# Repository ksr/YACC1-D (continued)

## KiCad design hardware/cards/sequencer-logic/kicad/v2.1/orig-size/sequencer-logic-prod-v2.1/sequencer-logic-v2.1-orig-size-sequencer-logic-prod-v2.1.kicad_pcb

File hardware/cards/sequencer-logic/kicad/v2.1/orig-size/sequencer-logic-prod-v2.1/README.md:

# sequencer-logic-v2.1-orig-size-sequencer-logic-prod-v2.1 — KiCad conversion

Generated 2026-09-23 by `tools/eagle_to_kicad_all.py` from the Eagle design `Sequencer-Logic-Prod-V2.1` in `hardware/cards/sequencer-logic/eagle/v2.1/orig size/`. **The Eagle files are the record of what was designed and built; this KiCad project is derived from them and is regenerated from scratch on every run of the tool** (hand edits here will be lost - once a card is edited in KiCad, remove it from the tool's list). This revision was never fabricated (or its build status is unknown, see `hardware/FABRICATED.md`).

## Files

| File | What it is |
|---|---|
| `sequencer-logic-v2.1-orig-size-sequencer-logic-prod-v2.1.kicad_pro` | project; OSH Park rules (6 mil track, 5 mil clearance, 10 mil drill, 4 mil annular) |
| `sequencer-logic-v2.1-orig-size-sequencer-logic-prod-v2.1.kicad_sch` | root sheet; 10 sub-sheet(s) `sequencer-logic-v2.1-orig-size-sequencer-logic-prod-v2.1-sheetN.kicad_sch` mirror the Eagle sheets |
| `sequencer-logic-v2.1-orig-size-sequencer-logic-prod-v2.1-eagle.kicad_sym` | project symbol library generated from the Eagle libraries used (units = Eagle gates) |
| `sequencer-logic-v2.1-orig-size-sequencer-logic-prod-v2.1.kicad_pcb` | the board: 4 copper layers, 106 footprints, 4408 track segments, 539 vias |
| `sequencer-logic-v2.1-orig-size-sequencer-logic-prod-v2.1-eagle.pretty/` | project footprint library extracted from the imported board |
| `reports/` | ERC (`erc.json`), DRC (`drc.json`), schematic PDF, board renders (`-top.png`, `-bottom.png`), netlist + `netlist-compare.txt` |

## Proof

Schematic-vs-board netlist comparison (`tools/kicad/compare_netlists.py`: every (reference, pad) partition must be identical): **MATCH (282/282 nets)**

```
  same connectivity, different net name: [('/Sheet 1/-DO-INT', '-DO-INT'), ('/Sheet 1/CNT-CLK', 'CNT-CLK'), ('/Sheet 1/COUNT-FAULT', 'COUNT-FAULT'), ('/Sheet 1/DO-HALT', 'DO-HALT'), ('/Sheet 1/HALT-CLR', 'HALT-CLR'), ('/Sheet 1/LD-INS-REG1', 'LD-INS-REG1'), ('/Sheet 1/UCODE-CLK', 'UCODE-CLK'), ('/Sheet 2/SPARE3', 'SPARE3'), ('/Sheet 3/INT-EDGE', 'INT-EDGE'), ('/Sheet 5/-FP-HALT', '-FP-HALT'), ('/Sheet 5/-HALT-CONT', '-HALT-CONT'), ('/Sheet 5/EXTERNAL-SINGLESTEP-CLK', 'EXTERNAL-SINGLESTEP-CLK'), ('/Sheet 5/FP-CLKL', 'FP-CLKL'), ('/Sheet 5/FP-SINGLE-STEP-CLK', 'FP-SINGLE-STEP-CLK'), ('/Sheet 5/FP-SS', 'FP-SS'), ('/Sheet 6/-ONE-OPERAND-SEL', '-ONE-OPERAND-SEL'), ('Net-(-INT-PULLUP0-Pad1)', 'N$49'), ('Net-(.0-PadA)', 'N$59'), ('Net-(IC1A-A1)', 'N$2'), ('Net-(IC1A-A2)', 'N$3'), ('Net-(IC1A-A3)', 'N$10'), ('Net-(IC1A-A4)', 'N$23'), ('Net-(IC1B-A1)', 'N$34'), ('Net-(IC1B-A2)', 'N$35'), ('Net-(IC1B-A3)', 'N$36'), ('Net-(IC1B-A4)', 'N$37'), ('Net-(IC2A-A1)', 'N$7'), ('Net-(IC2A-A2)', 'N$8'), ('Net-(IC2A-A3)', 'N$9'), ('Net-(IC2A-A4)', 'N$11'), ('Net-(IC2B-A1)', 'N$12'), ('Net-(IC2B-A2)', 'N$13'), ('Net-(IC2B-A3)', 'N$14'), ('Net-(IC2B-A4)', 'N$15'), ('Net-(IC3-D1)', 'N$19'), ('Net-(IC3-D2)', 'N$20'), ('Net-(IC3-D3)', 'N$21'), ('Net-(IC3-D4)', 'N$22'), ('Net-(IC4-D1)', 'N$5'), ('Net-(IC4-D2)', 'N$6'), ('Net-(IC4-D3)', 'N$17'), ('Net-(IC4-D4)', 'N$18'), ('Net-(IC5-UP)', 'N$1'), ('Net-(IC7A-O)', 'N$31'), ('Net-(IC7C-I0)', 'N$40'), ('Net-(IC10A-I1)', 'N$55'), ('Net-(IC10A-O)', 'COUNT-RESET'), ('Net-(IC10B-I0)', 'N$39'), ('Net-(IC10B-I1)', 'N$38'), ('Net-(IC10C-I0)', 'N$72'), ('Net-(IC10C-I1)', 'N$71'), ('Net-(IC10C-O)', 'N$60'), ('Net-(IC10D-O)', 'N$26'), ('Net-(IC11B-I)', 'N$27'), ('Net-(IC11B-O)', 'N$29'), ('Net-(IC11E-I)', 'N$42'), ('Net-(IC11E-O)', 'N$46'), ('Net-(IC11F-I)', 'N$43'), ('Net-(IC11F-O)', 'N$41'), ('Net-(IC12B-I0)', 'N$53'), ('Net-(IC12B-O)', 'N$58'), ('Net-(IC12C-I0)', 'N$28'), ('Net-(IC12C-I1)', 'N$24'), ('Net-(IC12D-O)', 'N$54'), ('Net-(IC21A-I1)', 'N$25'), ('Net-(IC21C-O)', 'N$48'), ('Net-(IC22B-CLK)', 'N$33'), ('Net-(IC23A-I0)', 'FP-RESET'), ('Net-(IC23B-I1)', 'FP-EXECUTE'), ('Net-(IC23C-O)', 'N$32'), ('Net-(IC24A-I0)', 'N$70'), ('Net-(IC24A-O)', 'N$67'), ('Net-(IC24B-I0)', 'N$56'), ('Net-(IC24B-I1)', 'N$52'), ('Net-(IC24D-O)', 'N$47'), ('Net-(IC29B-I1)', 'N$4'), ('Net-(IC29C-I0)', 'N$51'), ('Net-(IC29D-O)', 'N$57'), ('Net-(IC30A-O)', 'N$44'), ('Net-(IC31A-I0)', 'FP-FREERUN'), ('Net-(IC31C-I1)', 'HARD-RESET1'), ('Net-(IC31D-I1)', 'FP-CLKH'), ('Net-(IC33A-A1)', 'N$62'), ('Net-(IC33A-A2)', 'N$63'), ('Net-(IC33A-A3)', 'N$64'), ('Net-(IC33A-A4)', 'N$65'), ('Net-(IC33B-A1)', 'N$66'), ('Net-(IC33B-A2)', 'N$68'), ('Net-(IC33B-A3)', 'N$69'), ('Net-(IC33B-A4)', 'N$61'), ('Net-(IC35A-O)', 'N$45'), ('Net-(IC36C-O)', 'N$16'), ('Net-(PWR0-PadA)', 'N$30'), ('SINGLE-STEP{slash}WAIT', 'SINGLE-STEP/WAIT')]
```

## Readability

`tools/kicad/sch_overlaps.py` over every sheet: text over text 14, text over a symbol body 22, text crossed by a line 50, items off the drawing frame or on the title block 0. What is left is mostly the Eagle drawing itself (parts placed that close in Eagle) or KiCad drawing pin numbers centred on short pins.

## Residual ERC / DRC

ERC by type: endpoint_off_grid 89, isolated_pin_label 18, unconnected_wire_endpoint 14.
`isolated_pin_label` = the converter's per-net global labels (cosmetic); `power_pin_not_driven` / unused-unit notes are the same ones KiCad's own Eagle importer leaves. `unconnected_wire_endpoint` / `pin_not_connected` = wire stubs Eagle leaves bare (mostly net wires ending on a bus, which is drawn as graphics here); since 2026-09-23 the converter no longer hangs a label on every such end (that was most of the label clutter), so they show as KiCad warnings.

DRC by type: clearance 9, items_not_allowed 2, lib_footprint_mismatch 3, shorting_items 61, silk_edge_clearance 25, silk_over_copper 199, silk_overlap 199, starved_thermal 1, text_height 38, text_thickness 36, track_width 199; unconnected items 4; schematic parity 0.
Silk-over-pad and clearance notes reflect the Eagle design as drawn; unconnected items are Eagle airwires (parts the design left unrouted).

Converter: converted: 276 symbols, 1063 wires, 508 labels, 226 junctions, 1 bus lines, 25 no-connects

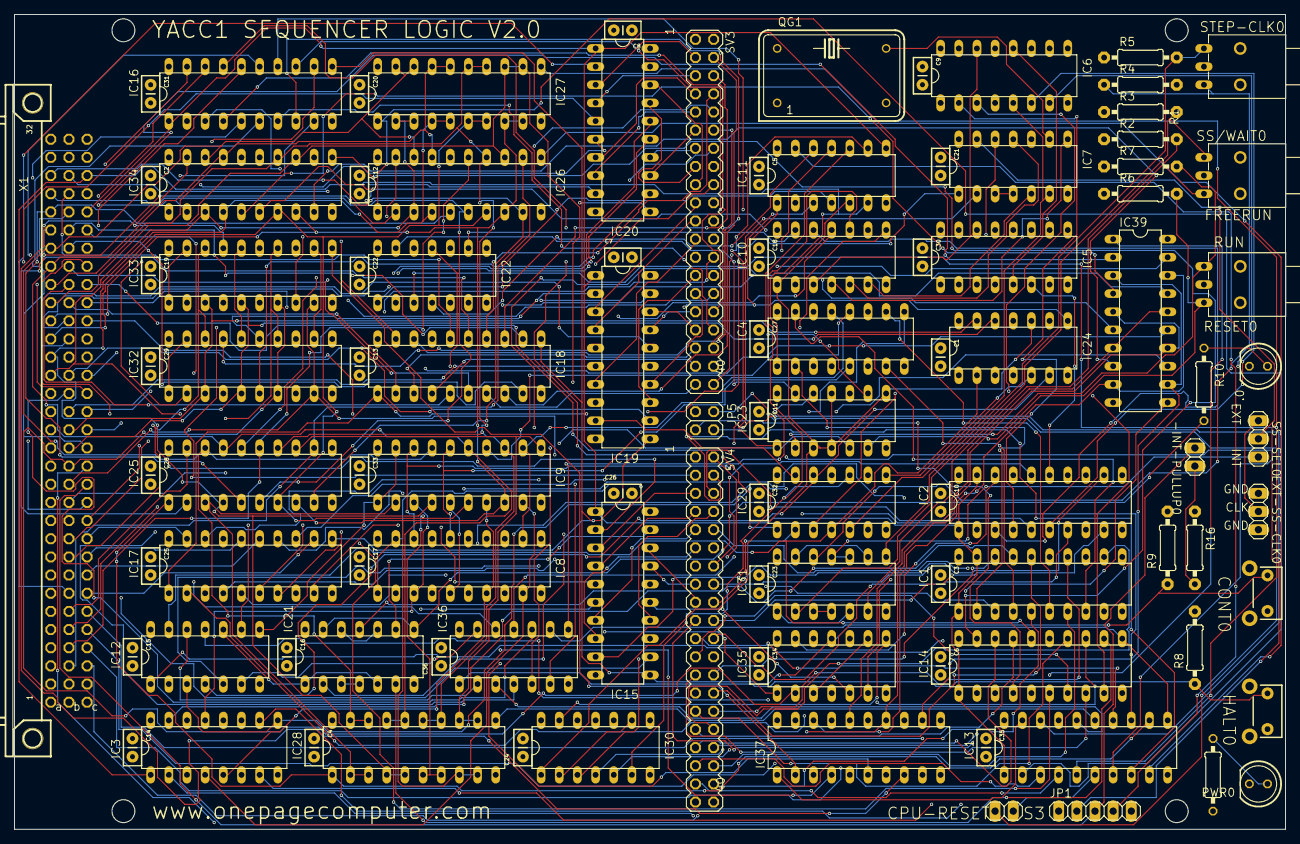
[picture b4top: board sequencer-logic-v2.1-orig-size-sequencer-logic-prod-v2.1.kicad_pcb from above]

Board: 4 copper layers, 177.8 x 114.0 mm, 106 parts (0 on the bottom side), 282 nets.

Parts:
-INT-PULLUP0: 1X02
.0: OUT; LED5MM
C1, C2, C3, C4, C5, C6, C7, C8, C9, C10, C11, C12, C13, C14, C15, C16, C17, C18, C19, C20, C21, C22, C23, C24, C25, C26, C27, C28, C29, C30, C31, C32, C33, C34, C35, C36: .1; CAP-PTH-SMALLEZ
CONT0: SWITCH-MOMENTARY-2SIDE_EZ; TACTILE-PTH-SIDEEZ
EXT-SS-CLK0: 1X03
HALT0: SWITCH-MOMENTARY-2SIDE_EZ; TACTILE-PTH-SIDEEZ
IC1, IC2, IC8, IC9, IC32, IC33, IC37, IC39: 74LS244N; DIL20
IC3, IC4: 74LS175N; DIL16
IC5, IC6: 74LS192N; DIL16
IC7, IC12, IC29: 74LS08N; DIL14
IC10, IC24, IC35: 74LS32N; DIL14
IC11, IC30, IC36: 74LS04N; DIL14
IC13, IC14, IC15, IC16, IC17, IC18, IC19, IC20, IC25, IC26, IC27, IC28, IC34: 74LS374N; DIL20
IC21, IC23, IC31: 74ALS02N; DIL14
IC22: 74LS74N; DIL14
JP1: 1X05
JP2: PINHD-1X2; 1X02
JP5: 2X02
PWR0: LED5MM
QG1: DIL14S
R1, R10: 330; 0207_10
R2, R3, R4, R5, R6, R7, R8, R9, R16: 10k; 0207_10
RESET0: 9070-1W
SS-SEL0: 1X03
SS/WAIT0: 9070-1W
STEP-CLK0: 9070-1W
SV3, SV4: MA20-2
UNK_HOLE_0: dummyfp0
UNK_HOLE_1: dummyfp1
UNK_HOLE_2: dummyfp2
UNK_HOLE_3: dummyfp3
X1: FABC96R

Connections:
-2-BYTE-OPERAND-SEL: IC13.16, IC33.1, IC33.19, IC36.3
-AC-LD: IC15.5, X1.C22
-AC-LD-INV: IC16.19, X1.C20
-AC-RD: IC15.2, X1.C21
-ALU-FUNC: IC16.6, X1.C15
-BRANCH-RD: IC13.2, IC26.1, IC27.1
-BUS-EN: IC1.1, IC1.19, IC2.1, IC2.19, IC11.8, IC13.1, IC14.1, IC15.1, IC16.1, IC17.1, IC18.1, IC19.1, IC20.1, X1.C28
-DO-INT: IC8.1, IC8.19, IC11.2
-FP-HALT: HALT0.2, IC36.1, R8.1
-HALT-CONT: CONT0.2, IC36.9, R9.1
-HL-SWAP: IC15.12, X1.C25
-INT: -INT-PULLUP0.2, JP1.3, X1.C13
-INT-JMP: IC13.12, IC25.1, IC28.1
-INTA: IC14.2, X1.C14
-IO-ADDR-LD: IC16.2, X1.C11
-IO-RD: IC18.6, X1.B25
-IO-WR: IC18.9, X1.B26
-MEM-CPU-RESET: JP2.1, JP5.2
-MEM-RD: IC18.2, X1.B23
-MEM-WR: IC18.5, X1.B24
-ONE-OPERAND-SEL: IC32.1, IC32.19, IC36.4, IC39.19
-REG-DN: IC19.16, X1.B21
-REG-FUNC-LD: IC20.5, X1.B8
-REG-FUNC-RD: IC20.2, X1.B7
-REG-LD-HI: IC36.12, X1.B20
-REG-LD-LO: IC36.10, X1.B18
-REG-RD-HI: IC19.12, X1.B19
-REG-RD-LO: IC19.6, X1.B17
-REG-UP: IC19.19, X1.B22
-RESET: IC3.1, IC4.1, IC11.6, X1.C30
-SR-LD: IC15.6, X1.C23
-TMP-REG-LD0: IC18.15, X1.B28
-TMP-REG-LD1: IC18.19, X1.B30
-TMP-REG-RD0: IC18.12, X1.B27
-TMP-REG-RD1: IC18.16, X1.B29
-VMA: IC16.5, X1.C12
ADDR-REG-ID0: IC37.18, IC39.9, IC39.18, X1.C3
ADDR-REG-ID1: IC37.16, IC39.7, IC39.16, X1.C4
ADDR-REG-ID2: IC37.14, IC39.5, IC39.14, X1.C5
ADDR-REG-ID3: IC37.12, IC39.3, IC39.12, X1.C6
ALU0: IC16.9, X1.C16
ALU1: IC16.12, X1.C17
ALU2: IC16.15, X1.C18
ALU3: IC16.16, X1.C19
BR-COND: IC29.1, X1.C24
BR-TEST: IC15.9, IC29.2
BRANCH-LD-HI: IC13.9, IC26.11
BRANCH-LD-LO: IC13.5, IC27.11
BUS-LATCH-CLK: IC13.11, IC14.11, IC15.11, IC16.11, IC17.11, IC18.11, IC19.11, IC20.11, IC35.11
CADDR0: IC2.16, SV4.14
CADDR1: IC2.14, SV4.16
CADDR2: IC2.12, SV4.18
CADDR3: IC2.9, SV4.20
CADDR4: IC2.7, SV4.22
CADDR5: IC2.5, SV4.24
CADDR6: IC1.18, SV4.26
CADDR7: IC1.16, SV4.28
CADDR8: IC1.14, SV4.30
CADDR9: IC1.12, SV4.32
CADDR10: IC1.9, SV4.34
CADDR11: IC1.7, SV4.36
CADDR12: IC1.5, SV4.38
CADDR13: IC1.3, SV4.2
CNT-CLK: IC2.18, IC35.13
COUNT-FAULT: IC2.3, IC10.12
COUNT-RESET: IC5.14, IC6.14, IC10.3
DATA0: IC9.2, IC25.3, IC26.3, IC27.2, IC27.3, IC28.2, IC28.3, IC34.3, X1.A19
DATA1: IC9.4, IC25.4, IC26.4, IC27.4, IC27.5, IC28.4, IC28.5, IC34.4, X1.A20
DATA2: IC9.6, IC25.7, IC26.7, IC27.6, IC27.7, IC28.6, IC28.7, IC34.7, X1.A21
DATA3: IC9.8, IC25.8, IC26.8, IC27.8, IC27.9, IC28.8, IC28.9, IC34.8, X1.A22
DATA4: IC9.11, IC25.13, IC26.13, IC27.12, IC27.13, IC28.12, IC28.13, IC34.13, X1.A23
DATA5: IC9.13, IC25.14, IC26.14, IC27.14, IC27.15, IC28.14, IC28.15, IC34.14, X1.A24
DATA6: IC9.15, IC25.17, IC26.17, IC27.16, IC27.17, IC28.16, IC28.17, IC34.17, X1.A25
DATA7: IC9.17, IC25.18, IC26.18, IC27.18, IC27.19, IC28.18, IC28.19, IC34.18, X1.A26
DATA8: IC25.2, IC26.2, X1.A27
DATA9: IC25.5, IC26.5, X1.A28
DATA10: IC25.6, IC26.6, X1.A29
DATA11: IC25.9, IC26.9, X1.A30
DATA12: IC25.12, IC26.12, X1.B3
DATA13: IC25.15, IC26.15, X1.B4
DATA14: IC25.16, IC26.16, X1.B5
DATA15: IC25.19, IC26.19, X1.B6
DEST-ADDR: IC13.19, IC37.1
DO-HALT: IC10.13, IC22.9
DO-INT: IC9.1, IC9.19, IC11.1, IC12.8
EXTERNAL-SINGLESTEP-CLK: EXT-SS-CLK0.2, SS-SEL0.3
FP-CLKH: IC31.12, R4.1, STEP-CLK0.3
FP-CLKL: IC31.8, R5.2, STEP-CLK0.1
FP-EXECUTE: IC23.6, R6.1, RESET0.3
FP-FREERUN: IC31.2, R3.2, SS/WAIT0.1
FP-HALT: IC12.12, IC36.2
FP-HALT-CONT: IC23.12, IC36.8
FP-RESET: IC23.2, R7.2, RESET0.1
FP-SINGLE-STEP-CLK: IC31.10, IC31.11, SS-SEL0.1
FP-SS: IC31.6, R2.1, SS/WAIT0.3
FREE-RUN: IC7.10, IC31.3, IC31.4
GND: .0.K, C1.2, C2.2, C3.2, C4.2, C5.2, C6.2, C7.2, C8.2, C9.2, C10.2, C11.2, C12.2, C13.2, C14.2, C15.2, C16.2, C17.2, C18.2, C19.2, C20.2, C21.2, C22.2, C23.2, C24.2, C25.2, C26.2, C27.2, C28.2, C29.2, C30.2, C31.2, C32.2, C33.2, C34.2, C35.2, C36.2, CONT0.1, EXT-SS-CLK0.1, EXT-SS-CLK0.3, HALT0.1, IC1.10, IC2.10, IC3.8, IC4.8, IC5.1, IC5.8, IC5.9, IC5.10, IC5.15, IC6.1, IC6.8, IC6.9, IC6.10, IC6.15, IC7.7, IC8.10, IC9.10, IC10.7, IC11.7, IC12.7, IC13.10, IC14.10, IC15.10, IC16.10, IC17.10, IC18.10, IC19.10, IC20.10, IC21.7, IC22.7, IC23.7, IC24.7, IC25.10, IC26.10, IC27.10, IC28.10, IC29.7, IC30.7, IC30.11, IC31.7, IC32.10, IC33.10, IC34.1, IC34.10, IC35.7, IC36.7, IC37.10, IC37.11, IC37.13, IC37.15, IC37.17, IC37.19, IC39.10, JP1.1, JP1.5, PWR0.K, QG1.7, R2.2, R3.1, R4.2, R5.1, R6.2, R7.1, SV4.39, SV4.40, X1.A1, X1.A32, X1.B1, X1.B32, X1.C1, X1.C32
HALT-CLR: IC22.13, IC23.13
HARD-RESET1: IC31.9, IC31.13
INT-EDGE: IC22.3, JP1.2
INT-EN: IC14.12, IC21.6
INT-LD-HI: IC14.6, IC25.11
INT-LD-LO: IC13.15, IC28.11
INT-START: IC14.9, IC24.9
IO-ADDR0: IC17.12, X1.C7
IO-ADDR1: IC17.15, X1.C8
IO-ADDR2: IC17.16, X1.C9
IO-ADDR3: IC17.19, X1.C10
LADDR-REG-ID0: IC17.2, IC39.11
LADDR-REG-ID1: IC17.5, IC39.13
LADDR-REG-ID2: IC17.6, IC39.15
LADDR-REG-ID3: IC17.9, IC39.17
LD-INS-REG: IC12.1, IC14.15
LD-INS-REG1: IC3.9, IC4.9, IC12.3
LREG-LD-HI: IC12.5, IC19.15
LREG-LD-ID0: IC20.16, IC32.11
LREG-LD-ID1: IC20.19, IC32.13
LREG-LD-ID2: IC19.2, IC32.15
LREG-LD-ID3: IC19.5, IC32.17
LREG-LD-LO: IC19.9, IC29.13
LREG-RD-ID0: IC20.6, IC32.2
LREG-RD-ID1: IC20.9, IC32.4
LREG-RD-ID2: IC20.12, IC32.6
LREG-RD-ID3: IC20.15, IC32.8
unnamed: IC5.5, IC6.12
unnamed: IC1.2, IC4.2
unnamed: IC1.4, IC4.7
unnamed: IC6.5, IC7.6, IC29.5
unnamed: IC4.4, IC8.18, IC9.18
unnamed: IC4.5, IC8.16, IC9.16
unnamed: IC2.2, IC6.3
unnamed: IC2.4, IC6.2
unnamed: IC2.6, IC6.6
unnamed: IC1.6, IC4.10
unnamed: IC2.8, IC6.7
unnamed: IC2.11, IC5.3
unnamed: IC2.13, IC5.2
unnamed: IC2.15, IC5.6
unnamed: IC2.17, IC5.7
unnamed: IC7.1, IC36.6
unnamed: IC4.12, IC8.14, IC9.14
unnamed: IC4.13, IC8.12, IC9.12
unnamed: IC3.4, IC8.9, IC9.9
unnamed: IC3.5, IC8.7, IC9.7
unnamed: IC3.12, IC8.5, IC9.5
unnamed: IC3.13, IC8.3, IC9.3
unnamed: IC1.8, IC4.15
unnamed: IC12.10, IC21.1, IC21.5
unnamed: IC21.3, IC21.4
unnamed: IC10.11, IC36.5
unnamed: IC11.3, IC21.2, IC24.8
unnamed: IC12.9, IC22.5
unnamed: IC11.4, IC22.1
unnamed: PWR0.A, R1.1
unnamed: IC7.3, IC7.4
unnamed: IC23.10, IC35.12
unnamed: IC22.11, IC35.6
unnamed: IC1.11, IC3.2
unnamed: IC1.13, IC3.7
unnamed: IC1.15, IC3.10
unnamed: IC1.17, IC3.15
unnamed: IC7.11, IC10.5
unnamed: IC7.8, IC10.4
unnamed: IC7.9, QG1.8
unnamed: IC11.12, IC22.4
unnamed: IC11.11, IC30.8
unnamed: IC11.13, JP1.4
unnamed: IC30.2, IC30.9
unnamed: IC35.3, IC35.9
unnamed: IC11.10, IC23.9
unnamed: IC24.11, IC35.10
unnamed: IC21.10, IC21.12
unnamed: -INT-PULLUP0.1, R16.2
unnamed: IC29.9, IC30.12
unnamed: IC24.5, IC29.8
unnamed: IC12.4, IC24.6, IC29.12
unnamed: IC12.11, IC35.4
unnamed: IC10.2, IC29.6
unnamed: IC24.4, IC30.13, IC35.8
unnamed: IC29.11, IC36.11
unnamed: IC12.6, IC36.13
unnamed: .0.A, R10.1
unnamed: IC10.8, IC30.3
unnamed: IC33.17, IC34.19, IC37.8
unnamed: IC33.2, IC34.2, IC39.2
unnamed: IC33.4, IC34.5, IC39.4
unnamed: IC33.6, IC34.6, IC39.6
unnamed: IC33.8, IC34.9, IC39.8
unnamed: IC33.11, IC34.12, IC37.2
unnamed: IC24.3, IC30.5
unnamed: IC33.13, IC34.15, IC37.4
unnamed: IC33.15, IC34.16, IC37.6
unnamed: IC24.1, IC30.4
unnamed: IC10.10, IC29.10, IC30.6
unnamed: IC10.9, IC29.3
OPERAND-CLK: IC14.19, IC34.11
OUT: IC21.8, IC21.13, R10.2, X1.C27
OUT-OFF: IC15.16, IC21.11
OUT-ON: IC15.19, IC21.9
READY: IC11.9, SV4.12
REG-LD-ID0: IC32.9, IC33.9, IC35.1, X1.B13
REG-LD-ID1: IC32.7, IC33.7, IC35.2, X1.B14
REG-LD-ID2: IC24.12, IC32.5, IC33.5, X1.B15
REG-LD-ID3: IC24.13, IC32.3, IC33.3, X1.B16
REG-RD-ID0: IC32.18, IC33.18, X1.B9
REG-RD-ID1: IC32.16, IC33.16, X1.B10
REG-RD-ID2: IC32.14, IC33.14, X1.B11
REG-RD-ID3: IC32.12, IC33.12, X1.B12
RESET: IC10.1, IC11.5, IC23.3, IC23.4, IC23.8, IC23.11, IC24.10, IC30.1
RUN: IC7.2, IC12.2, IC23.1, IC23.5
SINGLE-STEP-CLK: IC7.13, SS-SEL0.2
SINGLE-STEP/WAIT: IC7.12, IC31.1, IC31.5
SOFT-HALT: IC15.15, IC35.5
SPARE3: IC13.6, JP2.2
SRC-ADDR: IC14.5, IC39.1
U-2-BYTE-OPERAND-SEL: IC13.17, SV4.10
U-AC-LD: IC15.4, SV4.7
U-AC-LD-INV: IC16.18, SV4.3
U-AC-RD: IC15.3, SV4.5
U-ALU-FUNC: IC16.7, SV3.34
U-BRANCH-RD: IC13.3, SV4.35
U-HL-SWAP: IC15.13, SV4.13
U-INT-JMP: IC13.13, SV4.6
U-INTA: IC14.3, SV4.19
U-IO-ADDR-LD: IC16.3, SV3.30
U-IO-RD: IC18.7, SV3.39
U-IO-WR: IC18.8, SV3.4
U-MEM-RD: IC18.3, SV3.35
U-MEM-WR: IC18.4, SV3.37
U-REG-DN: IC19.17, SV3.31
U-REG-FUNC-LD: IC20.4, SV3.5
U-REG-FUNC-RD: IC20.3, SV3.3
U-REG-RD-HI: IC19.13, SV3.27
U-REG-RD-LO: IC19.7, SV3.23
U-REG-UP: IC19.18, SV3.33
U-SR-LD: IC15.7, SV4.9
U-TMP-REG-LD0: IC18.14, SV3.8
U-TMP-REG-LD1: IC18.18, SV3.12
U-TMP-REG-RD0: IC18.13, SV3.6
U-TMP-REG-RD1: IC18.17, SV3.10
U-VMA: IC16.4, SV3.32
UADDR-REG-ID0: IC17.3, SV3.14
UADDR-REG-ID1: IC17.4, SV3.16
UADDR-REG-ID2: IC17.7, SV3.18
UADDR-REG-ID3: IC17.8, SV3.20
UALU0: IC16.8, SV3.36
UALU1: IC16.13, SV3.38
UALU2: IC16.14, SV3.40
UALU3: IC16.17, SV4.1
UBR-TEST: IC15.8, SV4.11
UBRANCH-LD-HI: IC13.8, SV4.4
UBRANCH-LD-LO: IC13.4, SV4.37
UCODE-CLK: IC7.5, IC10.6
UCODE-COUNT-RESET: IC12.13, IC14.16, IC24.2, IC29.4
UDEST-ADDR: IC13.18, JP5.4
UINT-EN: IC14.13, SV4.27
UINT-LD-HI: IC14.7, SV4.23
UINT-LD-LO: IC13.14, SV4.21
UINT-START: IC14.8, SV4.25
UIO-ADDR0: IC17.13, SV3.22
UIO-ADDR1: IC17.14, SV3.24
UIO-ADDR2: IC17.17, SV3.26
UIO-ADDR3: IC17.18, SV3.28
ULD-INS-REG: IC14.14, SV4.29
UOPERAND-CLK: IC14.18, SV4.33
UOUT-OFF: IC15.17, SV4.15
UOUT-ON: IC15.18, SV4.17
UREG-LD-HI: IC19.14, SV3.29
UREG-LD-ID0: IC20.17, SV3.15
UREG-LD-ID1: IC20.18, SV3.17
UREG-LD-ID2: IC19.3, SV3.19
UREG-LD-ID3: IC19.4, SV3.21
UREG-LD-LO: IC19.8, SV3.25
UREG-RD-ID0: IC20.7, SV3.7
UREG-RD-ID1: IC20.8, SV3.9
UREG-RD-ID2: IC20.13, SV3.11
UREG-RD-ID3: IC20.14, SV3.13
USOFT-HALT: IC15.14, SV4.8
USPARE3: IC13.7, JP5.1
USRC-ADDR: IC14.4, JP5.3
UUCODE-COUNT-RESET: IC14.17, SV4.31
VCC: C1.1, C2.1, C3.1, C4.1, C5.1, C6.1, C7.1, C8.1, C9.1, C10.1, C11.1, C12.1, C13.1, C14.1, C15.1, C16.1, C17.1, C18.1, C19.1, C20.1, C21.1, C22.1, C23.1, C24.1, C25.1, C26.1, C27.1, C28.1, C29.1, C30.1, C31.1, C32.1, C33.1, C34.1, C35.1, C36.1, IC1.20, IC2.20, IC3.16, IC4.16, IC5.4, IC5.11, IC5.16, IC6.4, IC6.11, IC6.16, IC7.14, IC8.2, IC8.4, IC8.6, IC8.8, IC8.11, IC8.13, IC8.15, IC8.17, IC8.20, IC9.20, IC10.14, IC11.14, IC12.14, IC13.20, IC14.20, IC15.20, IC16.20, IC17.20, IC18.20, IC19.20, IC20.20, IC21.14, IC22.2, IC22.10, IC22.12, IC22.14, IC23.14, IC24.14, IC25.20, IC26.20, IC27.20, IC28.20, IC29.14, IC30.14, IC31.14, IC32.20, IC33.20, IC34.20, IC35.14, IC36.14, IC37.20, IC39.20, QG1.14, R1.2, R8.2, R9.2, R16.1, RESET0.2, SS/WAIT0.2, STEP-CLK0.2, SV3.1, SV3.2, X1.A2, X1.A31, X1.B2, X1.B31, X1.C2, X1.C31

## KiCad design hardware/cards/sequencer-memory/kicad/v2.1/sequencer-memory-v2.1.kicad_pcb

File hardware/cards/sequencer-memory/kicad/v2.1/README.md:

# sequencer-memory-v2.1 — KiCad conversion

Generated 2026-09-23 by `tools/eagle_to_kicad_all.py` from the Eagle design `Sequencer-Memory-V2.1` in `hardware/cards/sequencer-memory/eagle/v2.1/`. **The Eagle files are the record of what was designed and built; this KiCad project is derived from them and is regenerated from scratch on every run of the tool** (hand edits here will be lost - once a card is edited in KiCad, remove it from the tool's list). This revision was FABRICATED (see `hardware/FABRICATED.md`).

## Files

| File | What it is |
|---|---|
| `sequencer-memory-v2.1.kicad_pro` | project; OSH Park rules (6 mil track, 5 mil clearance, 10 mil drill, 4 mil annular) |
| `sequencer-memory-v2.1.kicad_sch` | root sheet; 4 sub-sheet(s) `sequencer-memory-v2.1-sheetN.kicad_sch` mirror the Eagle sheets |
| `sequencer-memory-v2.1-eagle.kicad_sym` | project symbol library generated from the Eagle libraries used (units = Eagle gates) |
| `sequencer-memory-v2.1.kicad_pcb` | the board: 4 copper layers, 63 footprints, 1681 track segments, 198 vias |
| `sequencer-memory-v2.1-eagle.pretty/` | project footprint library extracted from the imported board |
| `reports/` | ERC (`erc.json`), DRC (`drc.json`), schematic PDF, board renders (`-top.png`, `-bottom.png`), netlist + `netlist-compare.txt` |

## Proof

Schematic-vs-board netlist comparison (`tools/kicad/compare_netlists.py`: every (reference, pad) partition must be identical): **MATCH (106/106 nets)**

```
  same connectivity, different net name: [('/Sheet 3/ARD-RXIN', 'ARD-RXIN'), ('/Sheet 3/ARD-TXOUT', 'ARD-TXOUT'), ('/Sheet 3/FAULT', 'FAULT'), ('/Sheet 3/LD', 'LD'), ('/Sheet 3/LED-READY', 'LED-READY'), ('Net-(C19-Pad1)', 'N$8'), ('Net-(FAULT0-C)', 'N$27'), ('Net-(IC9-WP)', 'N$32'), ('Net-(IC15-AREF)', 'N$17'), ('Net-(IC15-PB6(XTAL1{slash}TOSC1))', 'N$6'), ('Net-(IC15-PB7(XTAL2{slash}TOSC2))', 'N$7'), ('Net-(IC15-PC0(ADC0))', 'N$30'), ('Net-(IC15-PC2(ADC2))', 'N$39'), ('Net-(JP3-DTR)', 'N$33'), ('Net-(JP3-VCC)', 'N$34'), ('Net-(LOADING0-C)', 'N$26'), ('Net-(PWR0-PadA)', 'N$1'), ('Net-(READY0-C)', 'N$25')]
```

## Readability

`tools/kicad/sch_overlaps.py` over every sheet: text over text 3, text over a symbol body 12, text crossed by a line 13, items off the drawing frame or on the title block 0. What is left is mostly the Eagle drawing itself (parts placed that close in Eagle) or KiCad drawing pin numbers centred on short pins.

## Residual ERC / DRC

ERC by type: unconnected_wire_endpoint 11.
`isolated_pin_label` = the converter's per-net global labels (cosmetic); `power_pin_not_driven` / unused-unit notes are the same ones KiCad's own Eagle importer leaves. `unconnected_wire_endpoint` / `pin_not_connected` = wire stubs Eagle leaves bare (mostly net wires ending on a bus, which is drawn as graphics here); since 2026-09-23 the converter no longer hangs a label on every such end (that was most of the label clutter), so they show as KiCad warnings.

DRC by type: lib_footprint_mismatch 2, shorting_items 1, silk_edge_clearance 9, silk_over_copper 199, silk_overlap 44, text_height 6, text_thickness 1, track_width 199; unconnected items 0; schematic parity 0.
Silk-over-pad and clearance notes reflect the Eagle design as drawn; unconnected items are Eagle airwires (parts the design left unrouted).

Converter: converted: 110 symbols, 584 wires, 398 labels, 82 junctions, 3 bus lines, 23 no-connects

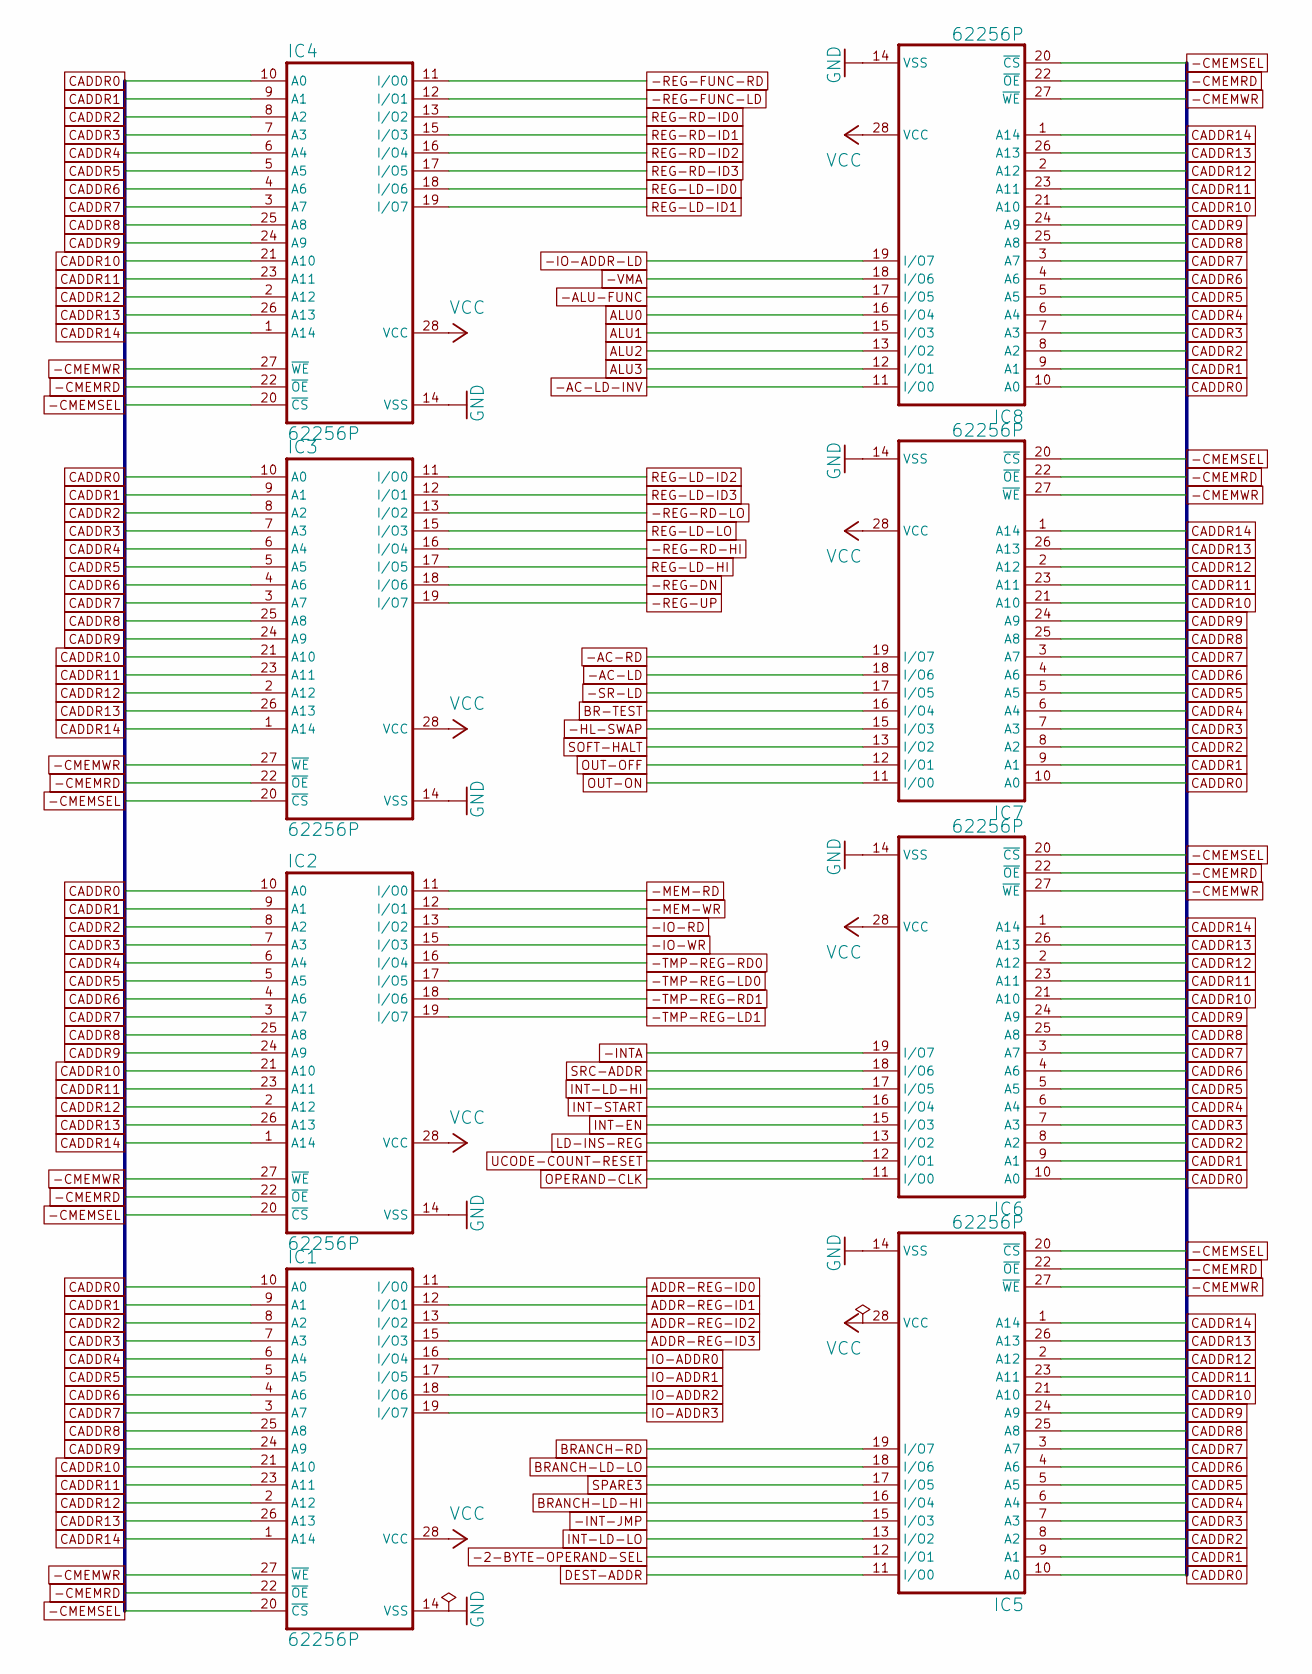
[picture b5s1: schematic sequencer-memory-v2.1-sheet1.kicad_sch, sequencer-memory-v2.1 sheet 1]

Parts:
IC1, IC2, IC3, IC4, IC5, IC6, IC7, IC8: 62256P; DIL28-6

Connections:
-2-BYTE-OPERAND-SEL: IC5.12 (I/O1); also elsewhere on the board
-AC-LD: IC7.18 (I/O6); also elsewhere on the board
-AC-LD-INV: IC8.11 (I/O0); also elsewhere on the board
-AC-RD: IC7.19 (I/O7); also elsewhere on the board
-ALU-FUNC: IC8.17 (I/O5); also elsewhere on the board
-CMEMRD: IC1.22 (~OE), IC2.22 (~OE), IC3.22 (~OE), IC4.22 (~OE), IC5.22 (~OE), IC6.22 (~OE), IC7.22 (~OE), IC8.22 (~OE); also elsewhere on the board
-CMEMSEL: IC1.20 (~CS), IC2.20 (~CS), IC3.20 (~CS), IC4.20 (~CS), IC5.20 (~CS), IC6.20 (~CS), IC7.20 (~CS), IC8.20 (~CS); also elsewhere on the board
-CMEMWR: IC1.27 (~WE), IC2.27 (~WE), IC3.27 (~WE), IC4.27 (~WE), IC5.27 (~WE), IC6.27 (~WE), IC7.27 (~WE), IC8.27 (~WE); also elsewhere on the board
-HL-SWAP: IC7.15 (I/O3); also elsewhere on the board
-INT-JMP: IC5.15 (I/O3); also elsewhere on the board
-INTA: IC6.19 (I/O7); also elsewhere on the board
-IO-ADDR-LD: IC8.19 (I/O7); also elsewhere on the board
-IO-RD: IC2.13 (I/O2); also elsewhere on the board
-IO-WR: IC2.15 (I/O3); also elsewhere on the board
-MEM-RD: IC2.11 (I/O0); also elsewhere on the board
-MEM-WR: IC2.12 (I/O1); also elsewhere on the board
-REG-DN: IC3.18 (I/O6); also elsewhere on the board
-REG-FUNC-LD: IC4.12 (I/O1); also elsewhere on the board
-REG-FUNC-RD: IC4.11 (I/O0); also elsewhere on the board
-REG-RD-HI: IC3.16 (I/O4); also elsewhere on the board
-REG-RD-LO: IC3.13 (I/O2); also elsewhere on the board
-REG-UP: IC3.19 (I/O7); also elsewhere on the board
-SR-LD: IC7.17 (I/O5); also elsewhere on the board
-TMP-REG-LD0: IC2.17 (I/O5); also elsewhere on the board
-TMP-REG-LD1: IC2.19 (I/O7); also elsewhere on the board
-TMP-REG-RD0: IC2.16 (I/O4); also elsewhere on the board
-TMP-REG-RD1: IC2.18 (I/O6); also elsewhere on the board
-VMA: IC8.18 (I/O6); also elsewhere on the board
ADDR-REG-ID0: IC1.11 (I/O0); also elsewhere on the board
ADDR-REG-ID1: IC1.12 (I/O1); also elsewhere on the board
ADDR-REG-ID2: IC1.13 (I/O2); also elsewhere on the board
ADDR-REG-ID3: IC1.15 (I/O3); also elsewhere on the board
ALU0: IC8.16 (I/O4); also elsewhere on the board
ALU1: IC8.15 (I/O3); also elsewhere on the board
ALU2: IC8.13 (I/O2); also elsewhere on the board
ALU3: IC8.12 (I/O1); also elsewhere on the board
BR-TEST: IC7.16 (I/O4); also elsewhere on the board
BRANCH-LD-HI: IC5.16 (I/O4); also elsewhere on the board
BRANCH-LD-LO: IC5.18 (I/O6); also elsewhere on the board
BRANCH-RD: IC5.19 (I/O7); also elsewhere on the board
CADDR0: IC1.10 (A0), IC2.10 (A0), IC3.10 (A0), IC4.10 (A0), IC5.10 (A0), IC6.10 (A0), IC7.10 (A0), IC8.10 (A0); also elsewhere on the board
CADDR1: IC1.9 (A1), IC2.9 (A1), IC3.9 (A1), IC4.9 (A1), IC5.9 (A1), IC6.9 (A1), IC7.9 (A1), IC8.9 (A1); also elsewhere on the board
CADDR2: IC1.8 (A2), IC2.8 (A2), IC3.8 (A2), IC4.8 (A2), IC5.8 (A2), IC6.8 (A2), IC7.8 (A2), IC8.8 (A2); also elsewhere on the board
CADDR3: IC1.7 (A3), IC2.7 (A3), IC3.7 (A3), IC4.7 (A3), IC5.7 (A3), IC6.7 (A3), IC7.7 (A3), IC8.7 (A3); also elsewhere on the board
CADDR4: IC1.6 (A4), IC2.6 (A4), IC3.6 (A4), IC4.6 (A4), IC5.6 (A4), IC6.6 (A4), IC7.6 (A4), IC8.6 (A4); also elsewhere on the board
CADDR5: IC1.5 (A5), IC2.5 (A5), IC3.5 (A5), IC4.5 (A5), IC5.5 (A5), IC6.5 (A5), IC7.5 (A5), IC8.5 (A5); also elsewhere on the board
CADDR6: IC1.4 (A6), IC2.4 (A6), IC3.4 (A6), IC4.4 (A6), IC5.4 (A6), IC6.4 (A6), IC7.4 (A6), IC8.4 (A6); also elsewhere on the board
CADDR7: IC1.3 (A7), IC2.3 (A7), IC3.3 (A7), IC4.3 (A7), IC5.3 (A7), IC6.3 (A7), IC7.3 (A7), IC8.3 (A7); also elsewhere on the board
CADDR8: IC1.25 (A8), IC2.25 (A8), IC3.25 (A8), IC4.25 (A8), IC5.25 (A8), IC6.25 (A8), IC7.25 (A8), IC8.25 (A8); also elsewhere on the board
CADDR9: IC1.24 (A9), IC2.24 (A9), IC3.24 (A9), IC4.24 (A9), IC5.24 (A9), IC6.24 (A9), IC7.24 (A9), IC8.24 (A9); also elsewhere on the board
CADDR10: IC1.21 (A10), IC2.21 (A10), IC3.21 (A10), IC4.21 (A10), IC5.21 (A10), IC6.21 (A10), IC7.21 (A10), IC8.21 (A10); also elsewhere on the board
CADDR11: IC1.23 (A11), IC2.23 (A11), IC3.23 (A11), IC4.23 (A11), IC5.23 (A11), IC6.23 (A11), IC7.23 (A11), IC8.23 (A11); also elsewhere on the board
CADDR12: IC1.2 (A12), IC2.2 (A12), IC3.2 (A12), IC4.2 (A12), IC5.2 (A12), IC6.2 (A12), IC7.2 (A12), IC8.2 (A12); also elsewhere on the board
CADDR13: IC1.26 (A13), IC2.26 (A13), IC3.26 (A13), IC4.26 (A13), IC5.26 (A13), IC6.26 (A13), IC7.26 (A13), IC8.26 (A13); also elsewhere on the board
CADDR14: IC1.1 (A14), IC2.1 (A14), IC3.1 (A14), IC4.1 (A14), IC5.1 (A14), IC6.1 (A14), IC7.1 (A14), IC8.1 (A14); also elsewhere on the board
DEST-ADDR: IC5.11 (I/O0); also elsewhere on the board
GND: IC1.14 (VSS), IC2.14 (VSS), IC3.14 (VSS), IC4.14 (VSS), IC5.14 (VSS), IC6.14 (VSS), IC7.14 (VSS), IC8.14 (VSS); also elsewhere on the board
INT-EN: IC6.15 (I/O3); also elsewhere on the board
INT-LD-HI: IC6.17 (I/O5); also elsewhere on the board
INT-LD-LO: IC5.13 (I/O2); also elsewhere on the board
INT-START: IC6.16 (I/O4); also elsewhere on the board
IO-ADDR0: IC1.16 (I/O4); also elsewhere on the board
IO-ADDR1: IC1.17 (I/O5); also elsewhere on the board
IO-ADDR2: IC1.18 (I/O6); also elsewhere on the board
IO-ADDR3: IC1.19 (I/O7); also elsewhere on the board
LD-INS-REG: IC6.13 (I/O2); also elsewhere on the board
OPERAND-CLK: IC6.11 (I/O0); also elsewhere on the board
OUT-OFF: IC7.12 (I/O1); also elsewhere on the board
OUT-ON: IC7.11 (I/O0); also elsewhere on the board
REG-LD-HI: IC3.17 (I/O5); also elsewhere on the board
REG-LD-ID0: IC4.18 (I/O6); also elsewhere on the board
REG-LD-ID1: IC4.19 (I/O7); also elsewhere on the board
REG-LD-ID2: IC3.11 (I/O0); also elsewhere on the board
REG-LD-ID3: IC3.12 (I/O1); also elsewhere on the board
REG-LD-LO: IC3.15 (I/O3); also elsewhere on the board
REG-RD-ID0: IC4.13 (I/O2); also elsewhere on the board
REG-RD-ID1: IC4.15 (I/O3); also elsewhere on the board
REG-RD-ID2: IC4.16 (I/O4); also elsewhere on the board
REG-RD-ID3: IC4.17 (I/O5); also elsewhere on the board
SOFT-HALT: IC7.13 (I/O2); also elsewhere on the board
SPARE3: IC5.17 (I/O5); also elsewhere on the board
SRC-ADDR: IC6.18 (I/O6); also elsewhere on the board
UCODE-COUNT-RESET: IC6.12 (I/O1); also elsewhere on the board
VCC: IC1.28 (VCC), IC2.28 (VCC), IC3.28 (VCC), IC4.28 (VCC), IC5.28 (VCC), IC6.28 (VCC), IC7.28 (VCC), IC8.28 (VCC); also elsewhere on the board

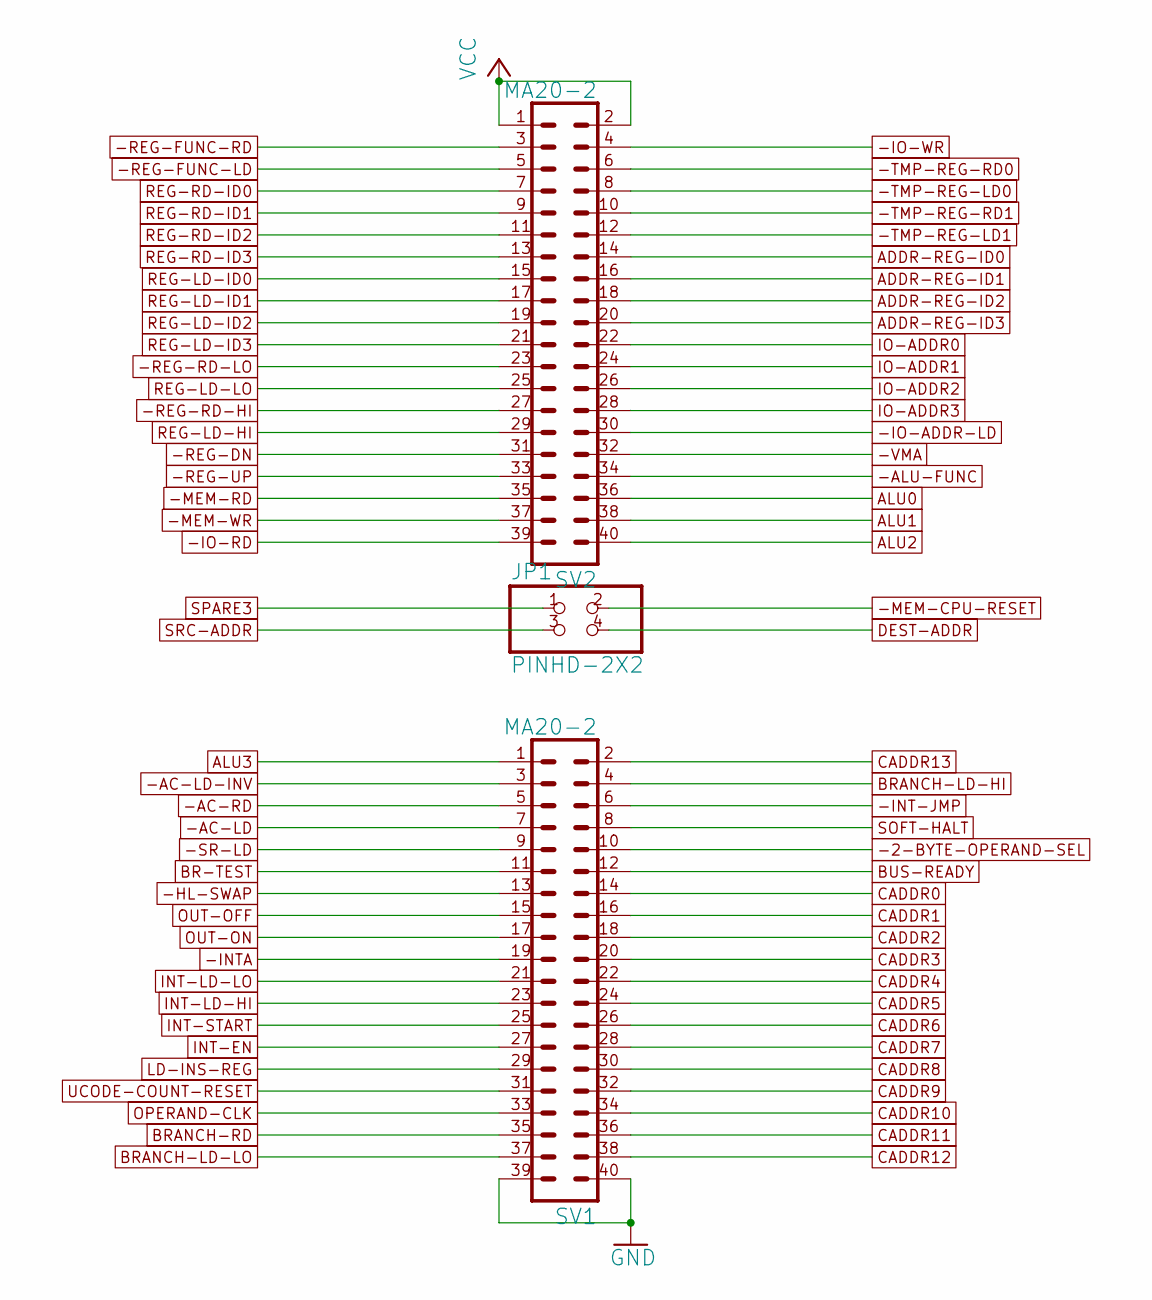
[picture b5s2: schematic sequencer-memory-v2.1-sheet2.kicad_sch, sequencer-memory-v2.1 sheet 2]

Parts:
JP1: PINHD-2X2; 2X02
SV1, SV2: MA20-2

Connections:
-2-BYTE-OPERAND-SEL: SV1.10; also elsewhere on the board
-AC-LD: SV1.7; also elsewhere on the board
-AC-LD-INV: SV1.3; also elsewhere on the board
-AC-RD: SV1.5; also elsewhere on the board
-ALU-FUNC: SV2.34; also elsewhere on the board
-HL-SWAP: SV1.13; also elsewhere on the board
-INT-JMP: SV1.6; also elsewhere on the board
-INTA: SV1.19; also elsewhere on the board
-IO-ADDR-LD: SV2.30; also elsewhere on the board
-IO-RD: SV2.39; also elsewhere on the board
-IO-WR: SV2.4; also elsewhere on the board
-MEM-CPU-RESET: JP1.2; also elsewhere on the board
-MEM-RD: SV2.35; also elsewhere on the board
-MEM-WR: SV2.37; also elsewhere on the board
-REG-DN: SV2.31; also elsewhere on the board
-REG-FUNC-LD: SV2.5; also elsewhere on the board
-REG-FUNC-RD: SV2.3; also elsewhere on the board
-REG-RD-HI: SV2.27; also elsewhere on the board
-REG-RD-LO: SV2.23; also elsewhere on the board
-REG-UP: SV2.33; also elsewhere on the board
-SR-LD: SV1.9; also elsewhere on the board
-TMP-REG-LD0: SV2.8; also elsewhere on the board
-TMP-REG-LD1: SV2.12; also elsewhere on the board
-TMP-REG-RD0: SV2.6; also elsewhere on the board
-TMP-REG-RD1: SV2.10; also elsewhere on the board
-VMA: SV2.32; also elsewhere on the board
ADDR-REG-ID0: SV2.14; also elsewhere on the board
ADDR-REG-ID1: SV2.16; also elsewhere on the board
ADDR-REG-ID2: SV2.18; also elsewhere on the board
ADDR-REG-ID3: SV2.20; also elsewhere on the board
ALU0: SV2.36; also elsewhere on the board
ALU1: SV2.38; also elsewhere on the board
ALU2: SV2.40; also elsewhere on the board
ALU3: SV1.1; also elsewhere on the board
BR-TEST: SV1.11; also elsewhere on the board
BRANCH-LD-HI: SV1.4; also elsewhere on the board
BRANCH-LD-LO: SV1.37; also elsewhere on the board
BRANCH-RD: SV1.35; also elsewhere on the board
BUS-READY: SV1.12; also elsewhere on the board
CADDR0: SV1.14; also elsewhere on the board
CADDR1: SV1.16; also elsewhere on the board
CADDR2: SV1.18; also elsewhere on the board
CADDR3: SV1.20; also elsewhere on the board
CADDR4: SV1.22; also elsewhere on the board
CADDR5: SV1.24; also elsewhere on the board
CADDR6: SV1.26; also elsewhere on the board
CADDR7: SV1.28; also elsewhere on the board
CADDR8: SV1.30; also elsewhere on the board
CADDR9: SV1.32; also elsewhere on the board
CADDR10: SV1.34; also elsewhere on the board
CADDR11: SV1.36; also elsewhere on the board
CADDR12: SV1.38; also elsewhere on the board
CADDR13: SV1.2; also elsewhere on the board
DEST-ADDR: JP1.4; also elsewhere on the board
GND: SV1.39, SV1.40; also elsewhere on the board
INT-EN: SV1.27; also elsewhere on the board
INT-LD-HI: SV1.23; also elsewhere on the board
INT-LD-LO: SV1.21; also elsewhere on the board
INT-START: SV1.25; also elsewhere on the board
IO-ADDR0: SV2.22; also elsewhere on the board
IO-ADDR1: SV2.24; also elsewhere on the board
IO-ADDR2: SV2.26; also elsewhere on the board
IO-ADDR3: SV2.28; also elsewhere on the board
LD-INS-REG: SV1.29; also elsewhere on the board
OPERAND-CLK: SV1.33; also elsewhere on the board
OUT-OFF: SV1.15; also elsewhere on the board
OUT-ON: SV1.17; also elsewhere on the board
REG-LD-HI: SV2.29; also elsewhere on the board
REG-LD-ID0: SV2.15; also elsewhere on the board
REG-LD-ID1: SV2.17; also elsewhere on the board
REG-LD-ID2: SV2.19; also elsewhere on the board
REG-LD-ID3: SV2.21; also elsewhere on the board
REG-LD-LO: SV2.25; also elsewhere on the board
REG-RD-ID0: SV2.7; also elsewhere on the board
REG-RD-ID1: SV2.9; also elsewhere on the board
REG-RD-ID2: SV2.11; also elsewhere on the board
REG-RD-ID3: SV2.13; also elsewhere on the board
SOFT-HALT: SV1.8; also elsewhere on the board
SPARE3: JP1.1; also elsewhere on the board
SRC-ADDR: JP1.3; also elsewhere on the board
UCODE-COUNT-RESET: SV1.31; also elsewhere on the board
VCC: SV2.1, SV2.2; also elsewhere on the board
